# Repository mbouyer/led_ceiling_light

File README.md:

# led_ceiling_light

Plafonier à LEDs 12V pour bateau, avec 2 puissances (puissance réduite en navigation)

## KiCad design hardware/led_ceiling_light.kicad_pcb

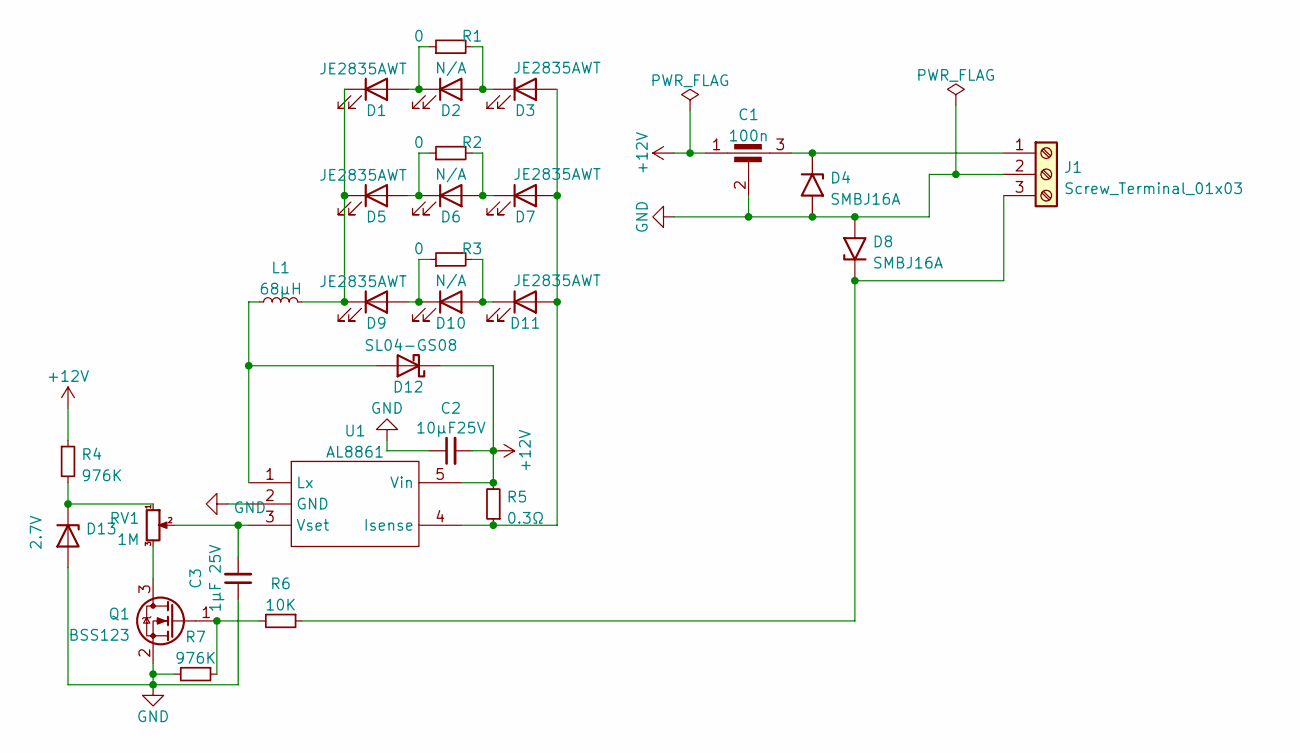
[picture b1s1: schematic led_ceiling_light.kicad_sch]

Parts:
C1: 100n; C_filter_0805
C2: 10µF25V; C_1210_3225Metric_Pad1.33x2.70mm_HandSolder
C3: 1µF 25V; C_0805_2012Metric_Pad1.18x1.45mm_HandSolder
D1, D3, D5, D7, D9, D11: JE2835AWT; LED_PLCC_2835_Handsoldering
D2, D6, D10: N/A; LED_PLCC_2835_Handsoldering
D4, D8: SMBJ16A; D_SMB_Handsoldering
D12: SL04-GS08; D_SMF
D13: 2.7V; D_MiniMELF_Handsoldering
J1: Screw_Terminal_01x03; TerminalBlock_TE_282834-3_1x03_P2.54mm_Horizontal
L1: 68µH; L_Taiyo-Yuden_NR-80xx_HandSoldering
Q1: BSS123; SOT-23
R1, R2, R3: 0; R_Axial_DIN0204_L3.6mm_D1.6mm_P7.62mm_Horizontal
R4, R7: 976K; R_0603_1608Metric_Pad0.98x0.95mm_HandSolder
R5: 0.3Ω; R_1206_3216Metric_Pad1.30x1.75mm_HandSolder
R6: 10K; R_0805_2012Metric_Pad1.20x1.40mm_HandSolder
RV1: 1M; Potentiometer_Piher_PT-10-V10_Vertical
U1: AL8861; TSOT-23-5_HandSoldering

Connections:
+12V: C1.1, C2.2, D12.1 (K), R4.1, R5.2, U1.5 (Vin)
GND: C1.2, C2.1, C3.1, D4.2 (A2), D8.2 (A2), D13.2 (A), J1.2, Q1.2 (S), R7.2, U1.2 (GND)
unnamed: C1.3, D4.1 (A1), J1.1
unnamed: C3.2, RV1.2, U1.3 (Vset)
unnamed: D1.1 (K), D5.1 (K), D9.1 (K), L1.2
unnamed: D1.2 (A), D2.1 (K), R1.1
unnamed: D2.2 (A), D3.1 (K), R1.2
unnamed: D5.2 (A), D6.1 (K), R2.1
unnamed: D6.2 (A), D7.1 (K), R2.2
unnamed: D8.1 (A1), J1.3, R6.1
unnamed: D9.2 (A), D10.1 (K), R3.1
unnamed: D10.2 (A), D11.1 (K), R3.2
unnamed: D3.2 (A), D7.2 (A), D11.2 (A), R5.1, U1.4 (Isense)
unnamed: D12.2 (A), L1.1, U1.1 (Lx)
unnamed: D13.1 (K), R4.2, RV1.1
unnamed: Q1.1 (G), R6.2, R7.1
unnamed: Q1.3 (D), RV1.3

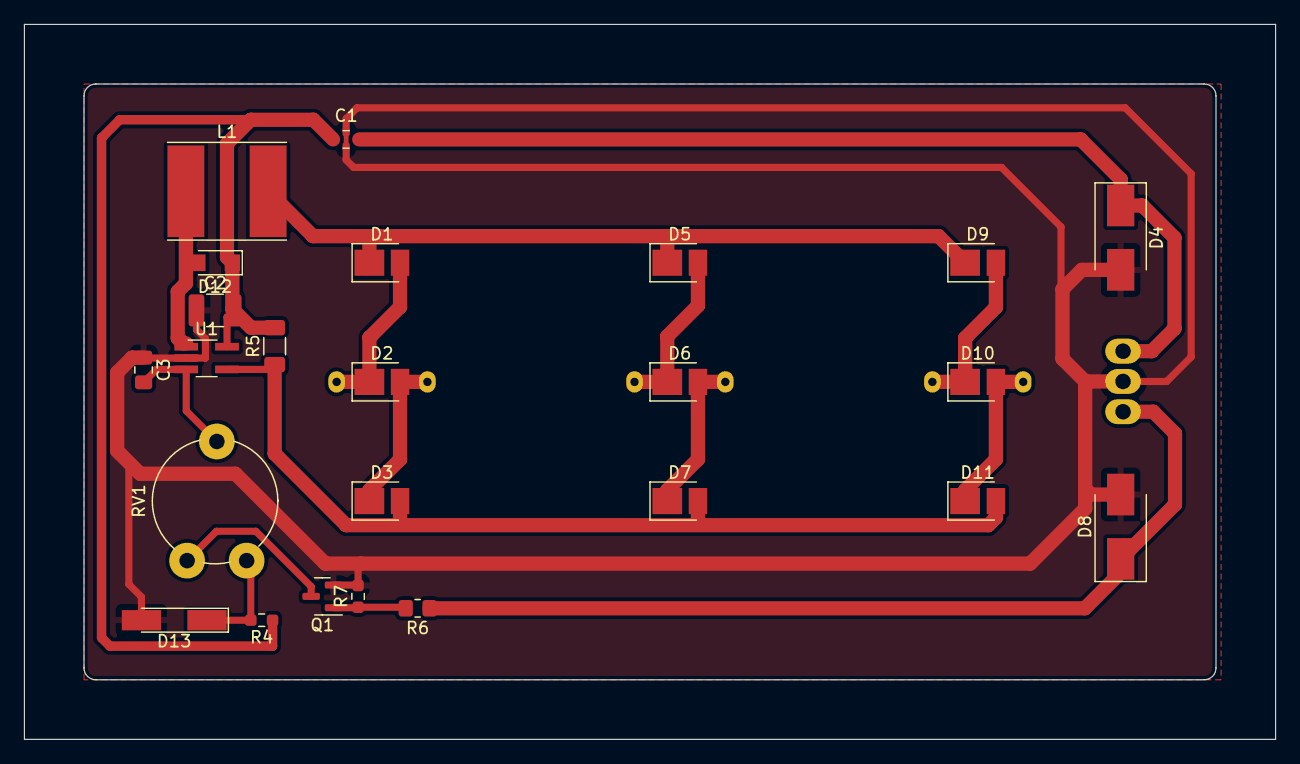
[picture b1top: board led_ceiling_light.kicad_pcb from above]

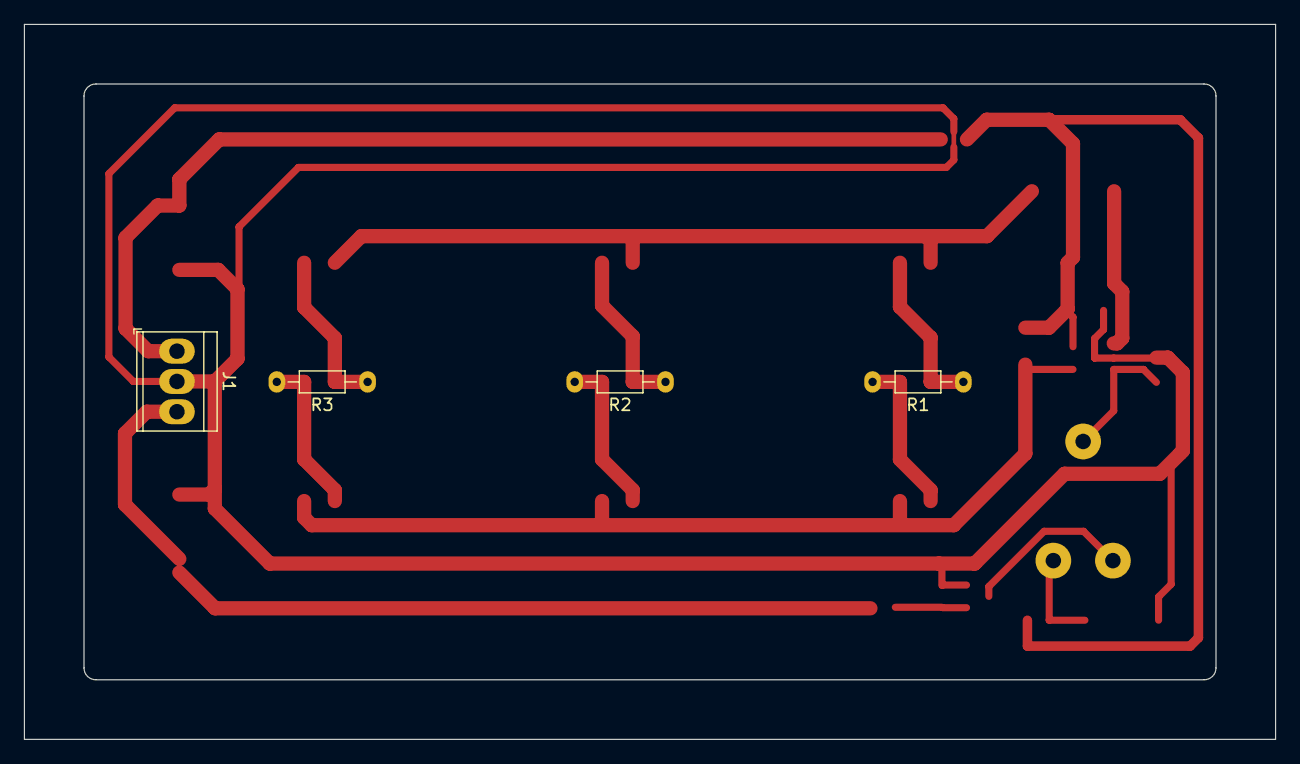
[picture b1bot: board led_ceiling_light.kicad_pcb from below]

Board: 2 copper layers, 105.0 x 60.0 mm, 28 parts (4 on the bottom side), 17 nets.

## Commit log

2022-12-13 Initial commit. Schematic almost complete; a few more footprint association needed.
2022-12-13 Fix some DRC issues; add more footprints.
2022-12-13 More part numbers and footprint
2022-12-13 One last P/N
2023-01-06 complete P/N and footprints
2023-01-06 Dedup resistor value
2023-01-06 Add PCB design
2023-01-27 normalise and update P/N, update footprint to match
2023-01-27 Update PCB after P/N adjustements
2023-01-27 Run cleanup tracks
2023-01-29 Final pass on part numbers
2023-01-31 shrink PCB by 5mm to make space for cable. Round corners
2023-01-31 Add 3d model for a box
2023-02-01 Sync with P/N update
2023-02-01 Add optional a 3rd LED in serie (so we can have a 3x2 or 3x3 matrix). Re-annotate whole schematic
2023-02-01 Cosmetic adjust tracks
2023-02-02 PCB: show PCB holder place
2023-02-02 Make room to the back for the connector, which implies a PCB much closer to the front.
2023-02-07 Increase clearance to 0.3mm
2023-02-09 Generate fabrication files
2023-02-10 Adjust connector drill size for BG9.S riverts
2023-02-13 Move conector back to the front (we can use BG9.S rivets), so move PCB closer to the back of the box again
2023-02-13 BG9.S rivets needs 1.3mm hole
2023-02-15 Add a hole in the back of the box, for better cooling
2023-02-15 Add a hole in the front box for a plexiglass window.
2023-02-15 Show plexiglass window on the PCB
2023-02-19 Add a way to project the front part of the box to draw the plexiglass shape for machining. Add generated files: back.stl, front.stl and front-plexi.dxf
2023-02-24 Fix D13 footprint
2023-04-25 Add photo
